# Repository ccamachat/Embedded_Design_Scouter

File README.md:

# ECE445L Final Lab

## Deliverables

The deliverables folder should contain documentation about your project as
outlined in the lab documents.

## HW

The hw folder should contain your schematic and board files for your PCB or
circuits. In labs 3-11, you will be creating schematics for your circuit
in EAGLE. A setup tutorial can be found
[here](https://www.shawnvictor.net/autodesk-eagle.html).

## SW

The sw folder should contain your application firmware and software written for
the lab. The sw/inc folder contains firmware drivers written for you by
Professor Valvano. Feel free to write your own (in fact, in some labs, you may
be required to write your own).

You can place any other source files in the sw/ folder. TAs will look at the
files you create and/or modify for software quality and for running your
project.

## Resources

A couple files are provided in the Resources folder so you don't have to keep
searching for that one TI document. Some of them are immediately useful, like
the TM4C datasheet. Others may be useful for your final project, like the
TM4C_System_Design_Guidelines page.

## Git and Github

We will extensively use Git and Github for managing lab projects. This makes it
easier for TAs to grade and help debug the project by allowing the students to
see commit histories, maintain a common project structure, collaborate with
partners, merge different codebases, and to debug work.

Two common ways of using Git and Github are [Github Desktop](https://desktop.github.com/) and the [command line](https://git-scm.com/downloads). [Tutorials](https://dev.to/mollynem/git-github--workflow-fundamentals-5496) are also abundant on the net for you to peruse. We've provided a cheatsheet for git in the Resources folder.

It is highly recommended to make the most out of Git, even if you've never used
it before. Version control will save you a lot of suffering, and tools like Git
or SVN are ubiquitous in the industry.

## Lab Report

Following the lab doc provided at the root of this project, the TAs request you
submit a lab report in Microsoft Word (or Pages, if you're a Mac user). Please
name it `EID_lab_LAB_NUMBER_report.pdf`. Templates are provided in the root dir.

## Team Members/ Contributors

Coty Camachat   - Physical Design & PCB Soldering/Verification, Code Review  
Neilan Garcia   - PCB Soldering, PCB Design, Code Review  
Ethan Syed      - Software encoding, Protocol Verification, Device Acquisition  
Phebe Tan       - Software encoding, documentation review  
Under Supervision of Profesor Jonathan Valvano

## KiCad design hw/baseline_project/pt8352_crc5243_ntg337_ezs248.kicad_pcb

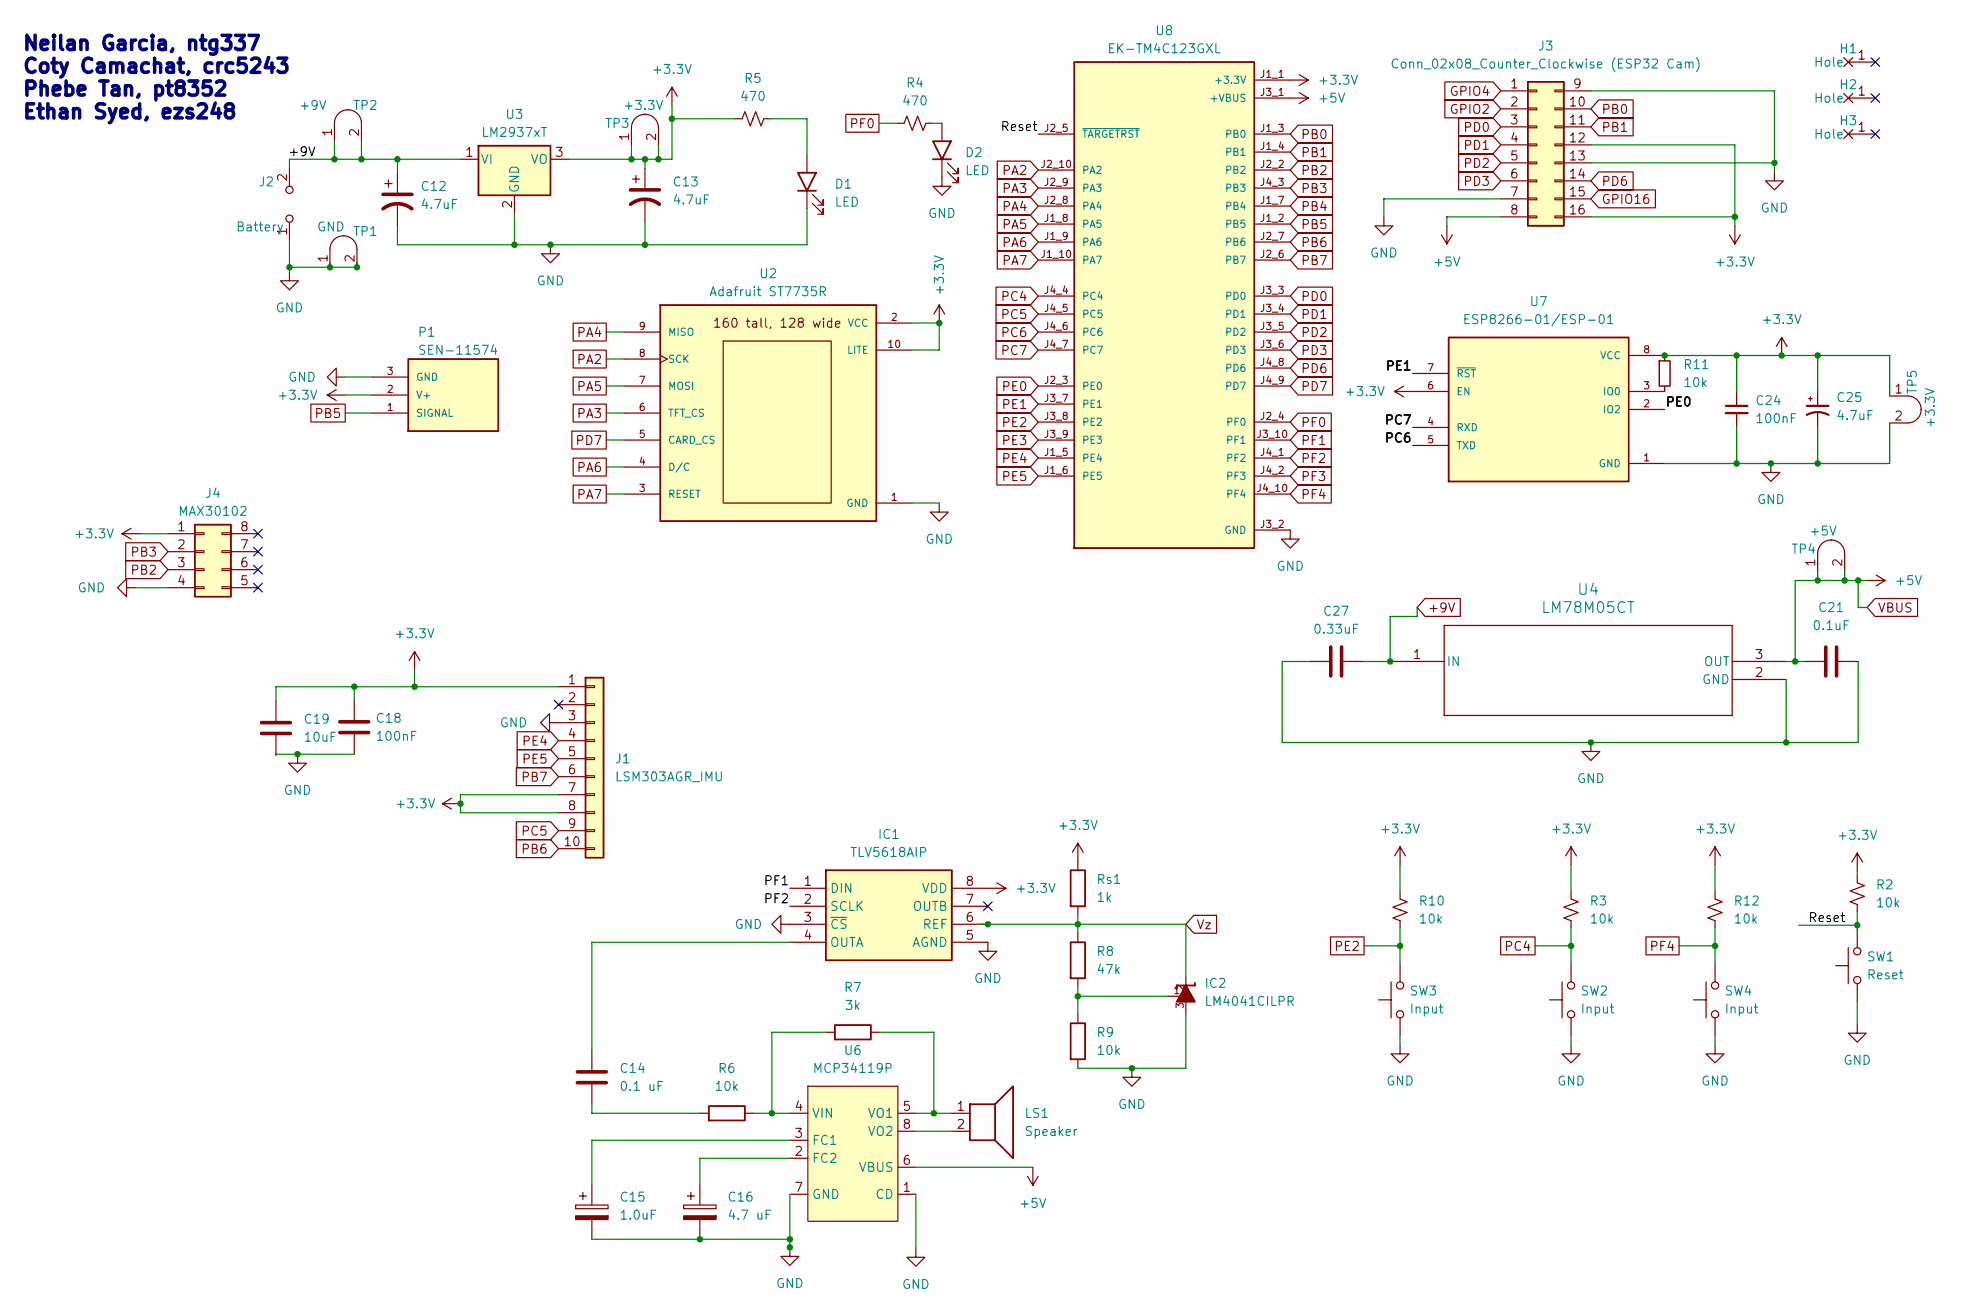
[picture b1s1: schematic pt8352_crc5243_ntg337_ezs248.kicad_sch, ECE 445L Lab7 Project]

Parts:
C12, C13, C25: 4.7uF; CP_Radial_Tantal200mil
C14: 0.1 uF; C_Axial_200mil
C15: 1.0uF; CP_Radial_Tantal200mil
C16: 4.7 uF; CP_Radial_Tantal200mil
C18, C24: 100nF; C_Axial_200mil
C19: 10uF; C_Axial_200mil
C21: 0.1uF; C_Axial_200mil
C27: 0.33uF; C_Axial_200mil
D1, D2: LED; LED_D5.0mm
H1, H2, H3: MountingHole_4_40
IC1: TLV5618AIP; DIP-8_W7.62mm_LongPads
IC2: LM4041CILPR; ti_LM4041CILPR
J1: LSM303AGR_IMU; Breakout_LSM303AGR_IMU
J2: Battery; Battery_Panasonic_CR1025-VSK_Vertical_CircularHoles
J3: Conn_02x08_Counter_Clockwise (ESP32 Cam); ESP32-CAM_v1
J4: MAX30102; MAX-30102_v1
LS1: Speaker; PinHeader_1x02_P2.54mm_Vertical
P1: SEN-11574; XDCR_SEN-11574
R2, R3, R6, R9, R10, R11, R12: 10k; R_Axial_DIN0204_L3.6mm_D1.6mm_P7.62mm_Horizontal
R4, R5: 470; R_Axial_DIN0204_L3.6mm_D1.6mm_P7.62mm_Horizontal
R7: 3k; R_Axial_DIN0204_L3.6mm_D1.6mm_P7.62mm_Horizontal
R8: 47k; R_Axial_DIN0204_L3.6mm_D1.6mm_P7.62mm_Horizontal
Rs1: 1k; R_Axial_DIN0204_L3.6mm_D1.6mm_P7.62mm_Horizontal
SW1: Reset; SW_PUSH_6mm
SW2, SW3, SW4: Input; SW_PUSH_6mm
TP1: GND; Testpoint_1x02_P2.54mm
TP2: +9V; Testpoint_1x02_P2.54mm
TP3, TP5: +3.3V; Testpoint_1x02_P2.54mm
TP4: +5V; Testpoint_1x02_P2.54mm
U2: Adafruit ST7735R; PinHeader_1x10_P2.54mm_Vertical
U3: LM2937xT; TO-220-3_Vertical
U4: LM78M05CT; T03B_TEX
U6: MCP34119P; DIP-8_W7.62mm_LongPads
U7: ESP8266-01/ESP-01; ai_thinker_ESP8266_01
U8: EK-TM4C123GXL; ti_EKTM4C123GXL

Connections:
+9V: C12.1, C27.2, J2.2 (B), TP2.1 (A), TP2.2 (B), U3.1 (VI), U4.1 (IN)
/Reset: R2.2, SW1.2, U8.J2_5 (~TARGETRST)
GPIO2: J3.2
GPIO4: J3.1
GPIO16: J3.15
unnamed: C14.2, R6.2
unnamed: D1.2 (A), R5.2
unnamed: D2.2 (A), R4.2
unnamed: C14.1, IC1.4 (OUTA)
unnamed: IC2.1, R8.2, R9.1
unnamed: C15.1, U6.3 (FC1)
unnamed: C16.1, U6.2 (FC2)
unnamed: R6.1, R7.2, U6.4 (VIN)
unnamed: LS1.1, R7.1, U6.5 (VO1)
unnamed: LS1.2, U6.8 (VO2)
unnamed: R11.2, U7.3 (IO0)
PA2: U2.8 (SCK), U8.J2_10 (PA2)
PA3: U2.6 (TFT_CS), U8.J2_9 (PA3)
PA4: U2.9 (MISO), U8.J2_8 (PA4)
PA5: U2.7 (MOSI), U8.J1_8 (PA5)
PA6: U2.4 (D/C), U8.J1_9 (PA6)
PA7: U2.3 (RESET), U8.J1_10 (PA7)
PB0: J3.10, U8.J1_3 (PB0)
PB1: J3.11, U8.J1_4 (PB1)
PB2: J4.3, U8.J2_2 (PB2)
PB3: J4.2, U8.J4_3 (PB3)
PB4: U8.J1_7 (PB4)
PB5: P1.1 (SIGNAL), U8.J1_2 (PB5)
PB6: J1.10, U8.J2_7 (PB6)
PB7: J1.6, U8.J2_6 (PB7)
PC4: R3.1, SW2.2, U8.J4_4 (PC4)
PC5: J1.9, U8.J4_5 (PC5)
PC6: U7.5 (TXD), U8.J4_6 (PC6)
PC7: U7.4 (RXD), U8.J4_7 (PC7)
PD0: J3.3, U8.J3_3 (PD0)
PD1: J3.4, U8.J3_4 (PD1)
PD2: J3.5, U8.J3_5 (PD2)
PD3: J3.6, U8.J3_6 (PD3)
PD6: J3.14, U8.J4_8 (PD6)
PD7: U2.5 (CARD_CS), U8.J4_9 (PD7)
PE0: U7.2 (IO2), U8.J2_3 (PE0)
PE1: U7.7 (~RST), U8.J3_7 (PE1)
PE2: R10.1, SW3.2, U8.J3_8 (PE2)
PE3: U8.J3_9 (PE3)
PE4: J1.4, U8.J1_5 (PE4)
PE5: J1.5, U8.J1_6 (PE5)
PF0: R4.1, U8.J2_4 (PF0)
PF1: IC1.1 (DIN), U8.J3_10 (PF1)
PF2: IC1.2 (SCLK), U8.J4_1 (PF2)
PF3: U8.J4_2 (PF3)
PF4: R12.1, SW4.2, U8.J4_10 (PF4)
VBUS: C21.1, J3.8, TP4.1 (A), TP4.2 (B), U4.3 (OUT), U6.6 (VBUS), U8.J3_1 (+VBUS)
Vz: IC1.6 (REF), IC2.2, R8.1, Rs1.2

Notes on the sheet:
Neilan Garcia, ntg337 Coty Camachat, crc5243 Phebe Tan, pt8352 Ethan Syed, ezs248

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
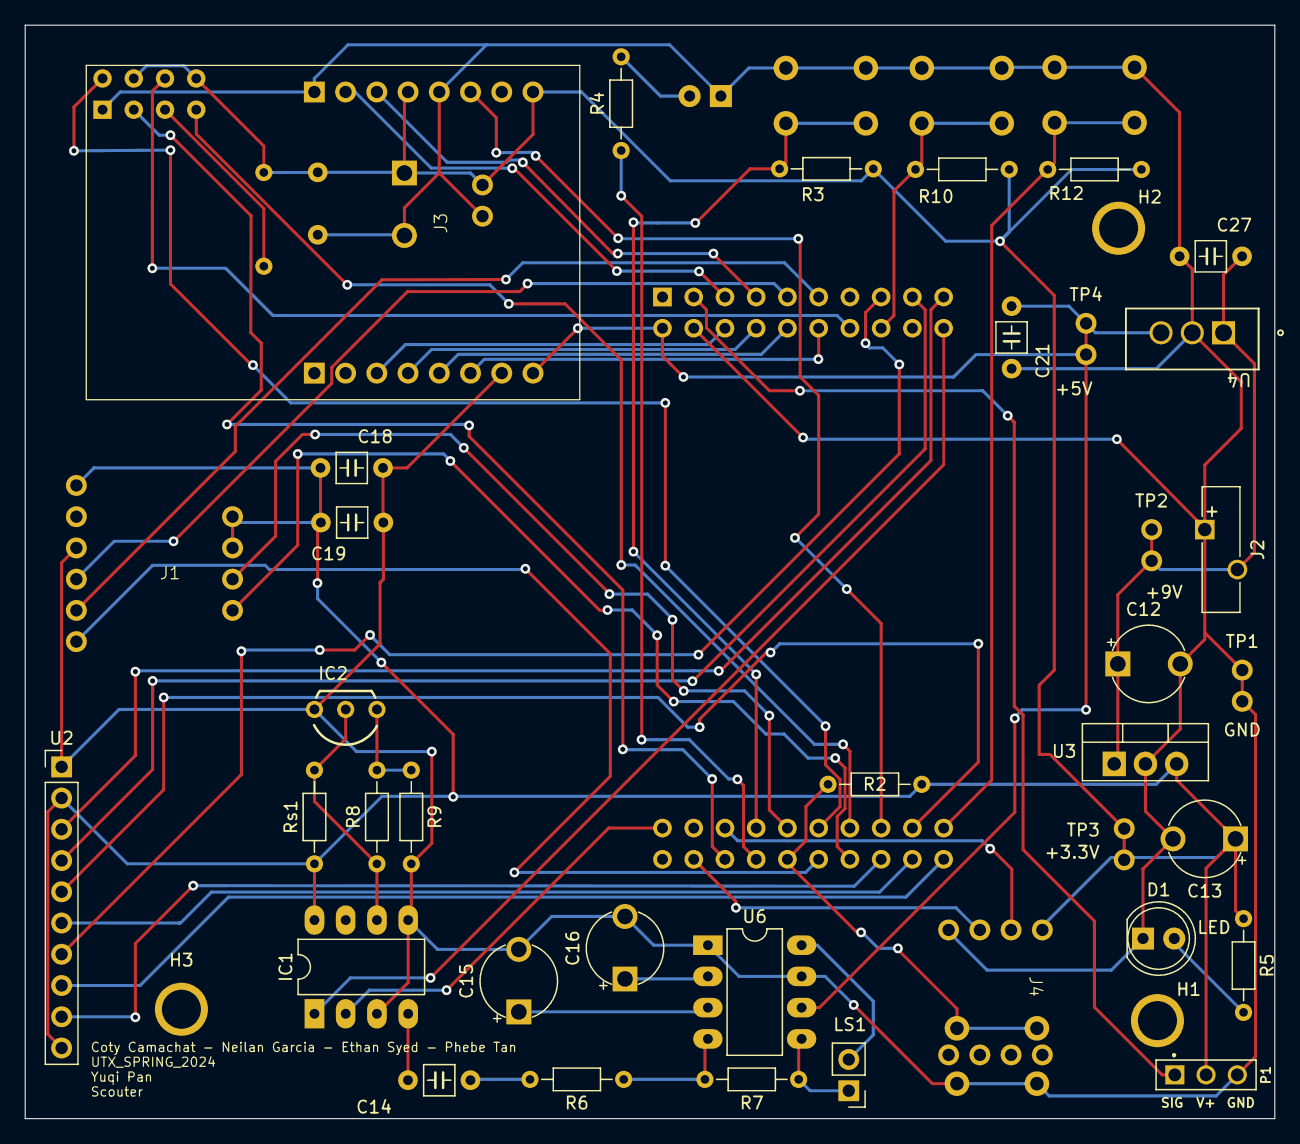
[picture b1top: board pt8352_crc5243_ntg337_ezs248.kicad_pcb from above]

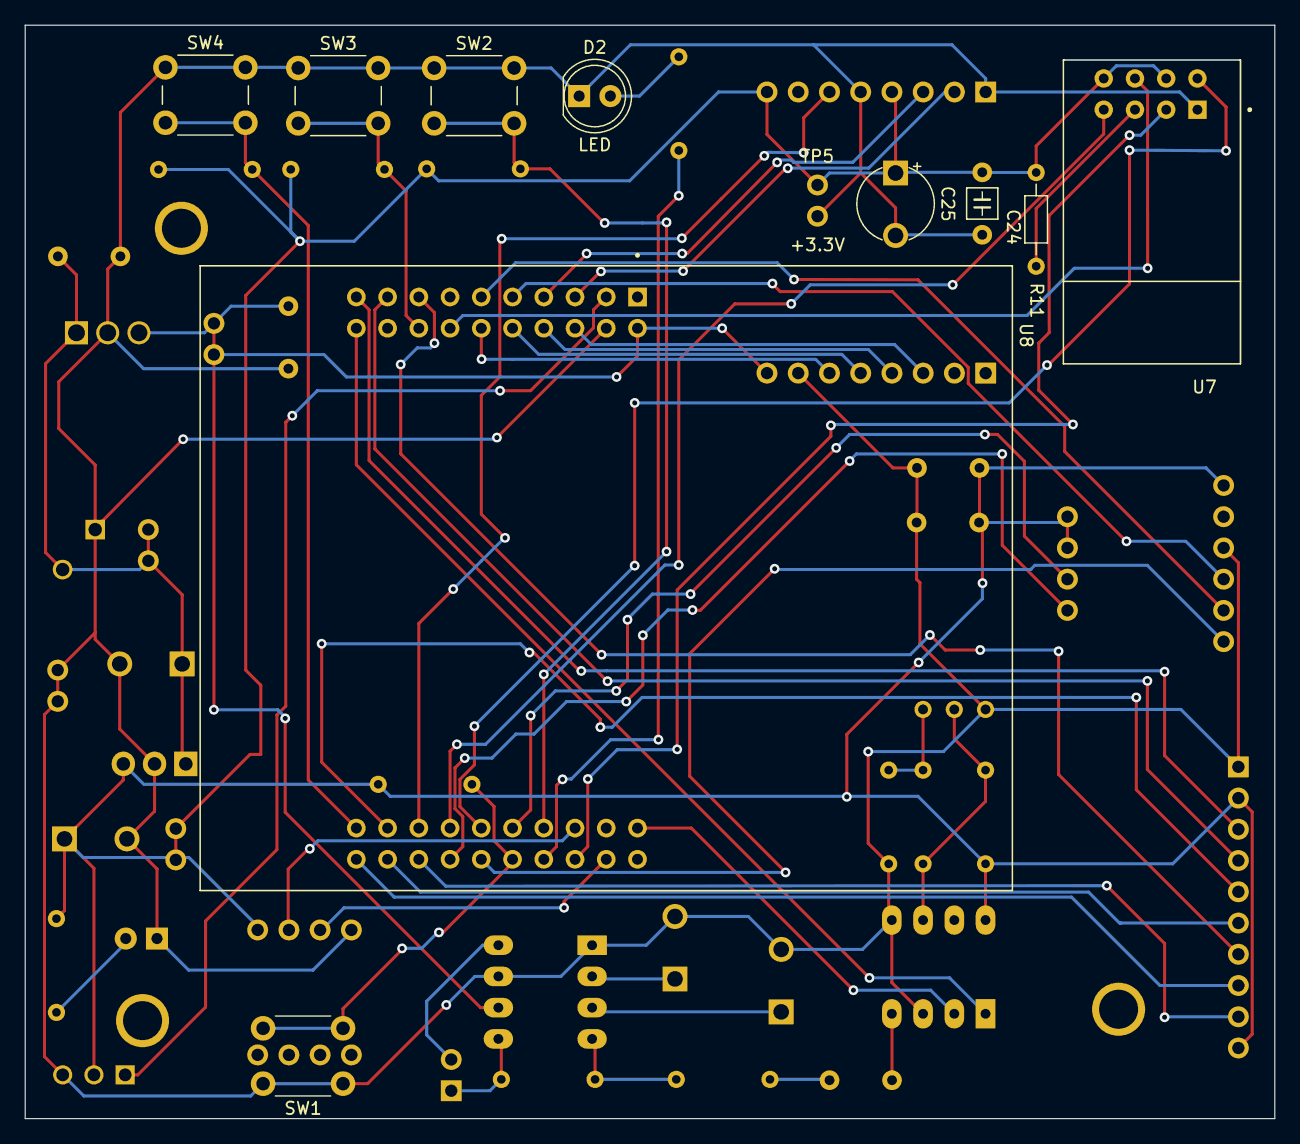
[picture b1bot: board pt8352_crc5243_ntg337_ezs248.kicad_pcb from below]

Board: 2 copper layers, 101.6 x 88.9 mm, 51 parts (11 on the bottom side), 49 nets.

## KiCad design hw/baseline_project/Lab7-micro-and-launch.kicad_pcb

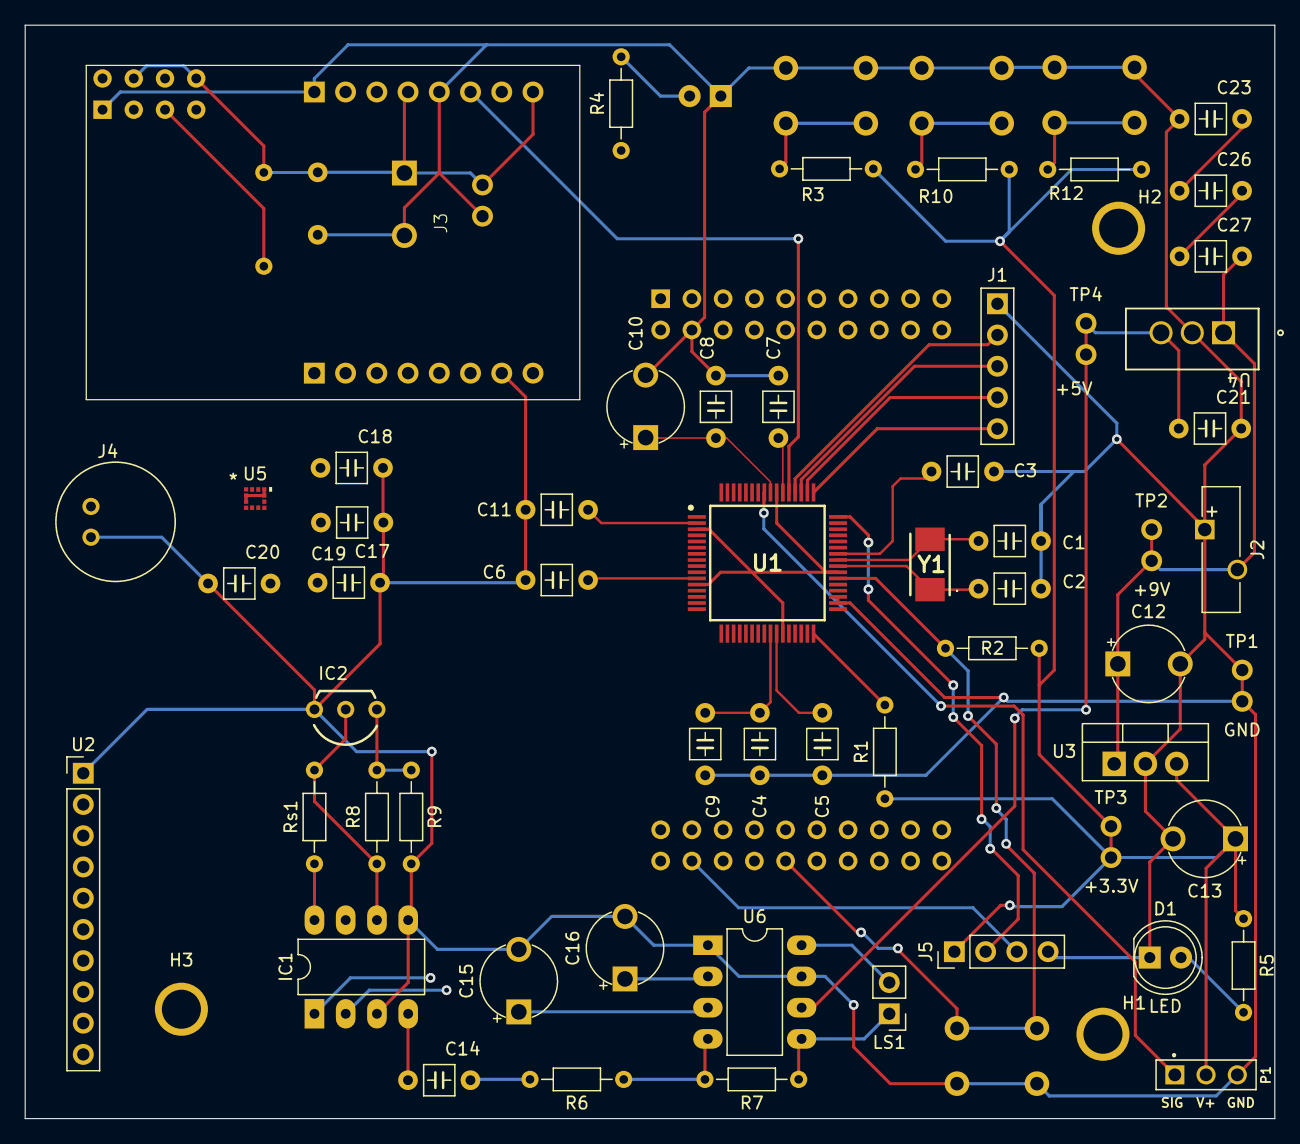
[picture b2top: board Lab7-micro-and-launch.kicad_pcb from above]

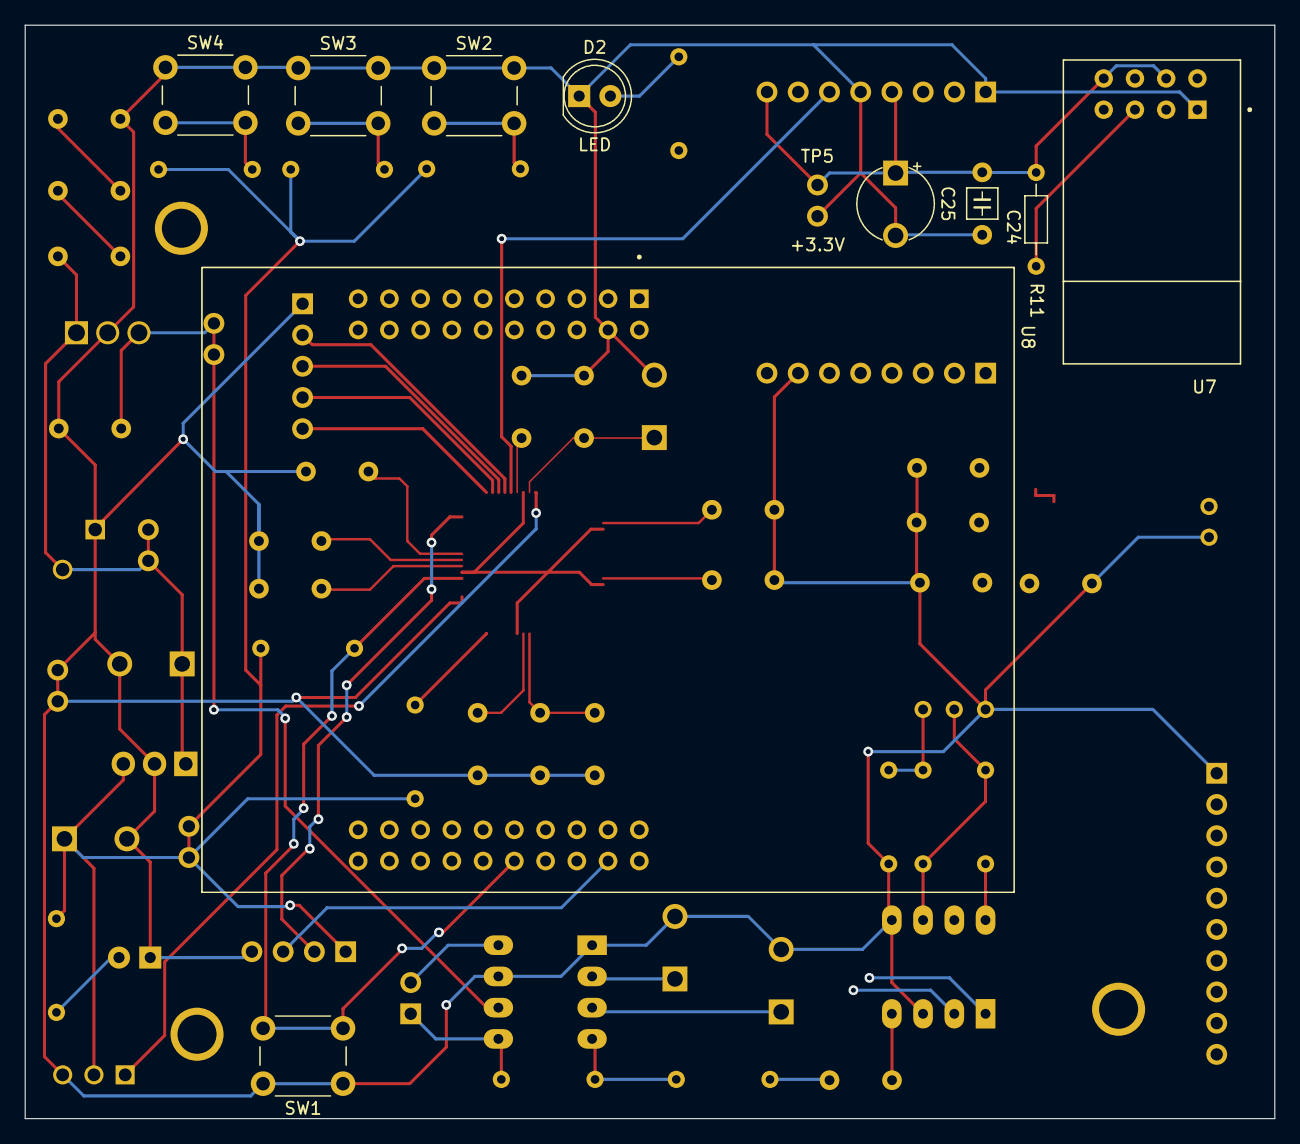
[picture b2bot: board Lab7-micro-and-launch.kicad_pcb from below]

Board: 2 copper layers, 101.6 x 88.9 mm, 71 parts (11 on the bottom side), 52 nets.

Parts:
C1, C2: 10pF C0G; C_Axial_200mil
C3, C9: 1uF; C_Axial_200mil
C4, C6, C7, C8, C21, C23, C26, C27: 0.1uF; C_Axial_200mil
C5, C11: 0.01uF; C_Axial_200mil
C10: 2.2uF; CP_Radial_Tantal200mil
C12, C13, C25: 4.7uF; CP_Radial_Tantal200mil
C14: 0.1 uF; C_Axial_200mil
C15: 1.0uF; CP_Radial_Tantal200mil
C16: 4.7 uF; CP_Radial_Tantal200mil
C17, C18, C24: 100nF; C_Axial_200mil
C19: 10uF; C_Axial_200mil
C20: 220nF; C_Axial_200mil
D1, D2: LED; LED_D5.0mm
H1, H2, H3: MountingHole_4_40
IC1: TLV5618AIP; DIP-8_W7.62mm_LongPads
IC2: LM4041CILPR; ti_LM4041CILPR
J1: JTAG; PinHeader_1x05_P2.54mm_Vertical
J2: Battery; Battery_Panasonic_CR1025-VSK_Vertical_CircularHoles
J3: Conn_02x08_Counter_Clockwise (ESP32 Cam); ESP32-CAM_v1
J4: Microphone; CUI_CMA-6542PF
J5: MAX30102; PinHeader_1x04_P2.54mm_Vertical
LS1: Speaker; PinHeader_1x02_P2.54mm_Vertical
P1: SEN-11574; XDCR_SEN-11574
R1: 1M; R_Axial_DIN0204_L3.6mm_D1.6mm_P7.62mm_Horizontal
R2, R3, R6, R9, R10, R11, R12: 10k; R_Axial_DIN0204_L3.6mm_D1.6mm_P7.62mm_Horizontal
R4, R5: 470; R_Axial_DIN0204_L3.6mm_D1.6mm_P7.62mm_Horizontal
R7: 3k; R_Axial_DIN0204_L3.6mm_D1.6mm_P7.62mm_Horizontal
R8: 47k; R_Axial_DIN0204_L3.6mm_D1.6mm_P7.62mm_Horizontal
Rs1: 1k; R_Axial_DIN0204_L3.6mm_D1.6mm_P7.62mm_Horizontal
SW1: Reset; SW_PUSH_6mm
SW2, SW3, SW4: Input; SW_PUSH_6mm
TP1: GND; Testpoint_1x02_P2.54mm
TP2: +9V; Testpoint_1x02_P2.54mm
TP3, TP5: +3.3V; Testpoint_1x02_P2.54mm
TP4: +5V; Testpoint_1x02_P2.54mm
U1: TM4C123GH6PMIR; QFP50P1200X1200X160-64N
U2: Adafruit ST7735R; PinHeader_1x10_P2.54mm_Vertical
U3: LM2937xT; TO-220-3_Vertical
U4: LM78M05CT; T03B_TEX
U5: LSM303AGRTR; SON_03AGRTR_STM
U6: MCP34119P; DIP-8_W7.62mm_LongPads
U7: ESP8266-01/ESP-01; ai_thinker_ESP8266_01
U8: EK-TM4C123GXL; ti_EKTM4C123GXL
Y1: ABM3-16.000MHZ-B2-T; ABM3

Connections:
+3.3V: C3.1, C5.1, C6.1, C7.1, C11.1, C13.1, C17.1, C18.1, C19.2, C24.1, C25.1, IC1.8 (VDD), J3.12, J3.16, J5.1, P1.2 (V+), R1.1, R2.1, R3.2, R5.1, R10.2, R11.1, R12.2, Rs1.1, TP3.1 (A), TP3.2 (B), TP5.1 (A), U1.2 (VDDA), U1.11 (VDD_1), U1.26 (VDD_2), U1.37 (VBAT), U1.42 (VDD_3), U1.54 (VDD_4), U2.2 (VCC), U2.10 (LITE), U3.3 (VO), U5.2 (CS_XL), U5.3 (CS_MAG), U5.9 (VDD), U5.10 (VDD_IO), U7.6 (EN), U7.8 (VCC), U8.J1_1 (+3.3V)
+9V: C12.1, C27.2, J2.2 (B), TP2.1 (A), TP2.2 (B), U3.1 (VI), U4.1 (IN)
/LDO: C4.1, C8.1, C9.1, C10.1, U1.25 (VDDC_1), U1.56 (VDDC_2)
/OSC1: C1.1, U1.41 (OSC1), Y1.2
/OSC2: C2.1, U1.40 (OSC0), Y1.1
/Reset: R2.2, SW1.2, U1.38 (~RST), U8.J2_5 (~TARGETRST)
/TCK: J1.2 (B), U1.52 (PC0/TCK/SWCLK)
/TDI: J1.4 (C), U1.50 (PC2/TDI)
/TDO: J1.5 (C), U1.49 (PC3/TDO/SWO)
/TMS: J1.3 (C), U1.51 (PC1/TMS/SWDIO)
GND: C1.2, C2.2, C3.2, C4.2, C5.2, C6.2, C7.2, C8.2, C9.2, C10.2, C11.2, C12.2, C13.2, C15.2, C16.2, C17.2, C18.2, C19.1, C20.1, C21.2, C23.1, C24.2, C25.2, D1.1 (K), D2.1 (K), IC1.3 (~CS), IC1.5 (AGND), IC2.3, J1.1 (A), J2.1 (A), J3.7, J3.9, J3.13, J4.2, J5.4, P1.3 (GND), R9.2, SW1.1, SW2.1, SW3.1, SW4.1, TP1.1 (A), TP1.2 (B), TP5.2 (B), U1.3 (GNDA), U1.12 (GND_1), U1.27 (GND_2), U1.34 (XOSC0), U1.35 (GNDX), U1.39 (GND_3), U1.55 (GND_4), U2.1 (GND), U3.2 (GND), U4.2 (GND), U5.8 (GND), U6.1 (CD), U6.7 (GND), U7.1 (GND), U8.J3_2 (GND)
unnamed: D1.2 (A), R5.2
unnamed: D2.2 (A), R4.2
unnamed: C14.1, IC1.4 (OUTA)
unnamed: IC2.1, R8.2, R9.1
PA2: U1.19 (PA2/SSI0C1K), U2.8 (SCK), U8.J2_10 (PA2)
PA3: U1.20 (PA3/SSI0FSS), U2.6 (TFT_CS), U8.J2_9 (PA3)
PA4: U1.21 (PA4/SSI0RX), U2.9 (MISO), U8.J2_8 (PA4)
PA5: U1.22 (PA5/SSI0TX), U2.7 (MOSI), U8.J1_8 (PA5)
PA6: U1.23 (PA6), U2.4 (D/C), U8.J1_9 (PA6)
PA7: U1.24 (PA7), U2.3 (RESET), U8.J1_10 (PA7)
PB0: J3.10, U1.45 (PB0/USB0ID), U8.J1_3 (PB0)
PB1: J3.11, U1.46 (PB1/USB0VBUS), U8.J1_4 (PB1)
PB2: J5.3, U1.47 (PB2/I2C0SCL), U8.J2_2 (PB2)
PB3: J5.2, U1.48 (PB3/I2C0SDA), U8.J4_3 (PB3)
PB4: U1.58 (PB4), U8.J1_7 (PB4)
PB5: P1.1 (SIGNAL), U1.57 (PB5), U8.J1_2 (PB5)
PB6: U1.1 (PB6), U5.11 (INT_2_XL), U8.J2_7 (PB6)
PB7: U1.4 (PB7), U5.7 (INT_MAG/DRDY), U8.J2_6 (PB7)
PC4: R3.1, SW2.2, U1.16 (PC4), U8.J4_4 (PC4)
PC5: U1.15 (PC5), U5.12 (INT_1_XL), U8.J4_5 (PC5)
PC6: U1.14 (PC6), U7.5 (TXD), U8.J4_6 (PC6)
PC7: U1.13 (PC7), U7.4 (RXD), U8.J4_7 (PC7)
PD0: J3.3, U1.61 (PD0), U8.J3_3 (PD0)
PD1: J3.4, U1.62 (PD1)
PD2: J3.5, U1.63 (PD2), U8.J3_4 (PD1), U8.J3_5 (PD2)
PD3: J3.6, U1.64 (PD3), U8.J3_6 (PD3)
PD6: J3.14, U1.53 (PD6), U8.J4_8 (PD6)
PD7: U1.10 (PD7), U2.5 (CARD_CS), U8.J4_9 (PD7)
PE0: U1.9 (PE0), U7.2 (IO2), U8.J2_3 (PE0)
PE1: U1.8 (PE1), U7.7 (~RST), U8.J3_7 (PE1)
PE2: R10.1, SW3.2, U1.7 (PE2), U8.J3_8 (PE2)
PE3: J4.1, U1.6 (PE3), U8.J3_9 (PE3)
PE4: U1.59 (PE4), U5.1 (SCL/SPC), U8.J1_5 (PE4)
PE5: U1.60 (PE5), U5.4 (SDA/SDI/SDO), U8.J1_6 (PE5)
PF0: R4.1, U1.28 (PF0), U8.J2_4 (PF0)
PF1: IC1.1 (DIN), U1.29 (PF1), U8.J3_10 (PF1)
PF2: IC1.2 (SCLK), U1.30 (PF2), U8.J4_1 (PF2)
PF3: U1.31 (PF3), U8.J4_2 (PF3)
PF4: R12.1, SW4.2, U1.5 (PF4), U8.J4_10 (PF4)
VBUS: C21.1, J3.8, TP4.1 (A), TP4.2 (B), U4.3 (OUT), U6.6 (VBUS), U8.J3_1 (+VBUS)
Vz: IC1.6 (REF), IC2.2, R8.1, Rs1.2

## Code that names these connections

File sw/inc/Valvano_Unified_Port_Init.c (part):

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// Port A drives the ST7735 LCD 
//
// Backlight (pin 10) connected to +3.3 V
// MISO      (pin 9)  connected to PA4
// SCK       (pin 8)  connected to PA2 (SSI0Clk)
// MOSI      (pin 7)  connected to PA5 (SSI0Tx)
// TFT_CS    (pin 6)  connected to PA3 (SSI0Fss)
// CARD_CS   (pin 5)  connected to PB0 (GPIO)
// Data/CMD  (pin 4)  connected to PA6 (GPIO), high for data, low for command
// RESET     (pin 3)  connected to PA7 (GPIO)
// VCC       (pin 2)  connected to +3.3 V
// Gnd       (pin 1)  connected to ground
//
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  SYSCTL_RCGCGPIO_R     |= 0x01;            // Activate port A
  while((SYSCTL_PRGPIO_R & 0x01)==0){};     // allow time for clock to start
    
  GPIO_PORTA_DIR_R      |= 0xC8;            // make PA3,6,7 out
  GPIO_PORTA_AFSEL_R    &= ~0xC8;           // disable alt funct on PA3,6,7
  GPIO_PORTA_DEN_R      |= 0xC8;            // enable digital I/O on PA3,6,7
  
  // configure PA3,6,7 as GPIO
  GPIO_PORTA_PCTL_R      = (GPIO_PORTA_PCTL_R
                         & 0x00FF0FFF)
                         + 0x00000000;
  
  GPIO_PORTA_AMSEL_R    &= ~0xC8;           // disable analog functionality on PA3,6,7

  // initialize SSI0
  GPIO_PORTA_AFSEL_R    |= 0x2C;            // enable alt funct on PA2,3,5
  GPIO_PORTA_DEN_R      |= 0x2C;            // enable digital I/O on PA2,3,5
 
  // configure PA2,3,5 as SSI
  GPIO_PORTA_PCTL_R      = (GPIO_PORTA_PCTL_R
                         & 0xFF0F00FF)
                         + 0x00202200;
  
  GPIO_PORTA_AMSEL_R    &= ~0x2C;           // disable analog functionality on PA2,3,5
  SSI0_CR1_R            &= ~SSI_CR1_SSE;    // disable SSI
  SSI0_CR1_R            &= ~SSI_CR1_MS;     // master mode
  
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// ----------------    PORT B Initialization   --------------------------------
// ----------------------------------------------------------------------------
//
// PB7 = PWM Ouptut to JP6 (M0PWM1)
// PB6 = PWM Output to Motor (M0PWM0)
// PB5 = ADC Input (AIN11)
// PB4 = Timer Capture input (T1CCP0)
// PB3 = GPIO 
// PB2 = GPIO/I2C0
// PB1 = GPIO/I2C0CL
// PB0 = ST7735 Card CS

void Port_B_Init(void){ 
  
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  SYSCTL_RCGCGPIO_R     |= 0x02;            // activate port B
  while((SYSCTL_PRGPIO_R & 0x02) == 0){};   // Wait
  
  // ---------------  Initialize PB7 as M0PWM1  -----------------------  

  GPIO_PORTB_AFSEL_R    |=  0x80;           // enable alt funct on PB7
  GPIO_PORTB_PCTL_R     &= ~0xF0000000;     // configure PB7 as M0PWM1
  GPIO_PORTB_PCTL_R     |=  0x40000000;
  GPIO_PORTB_AMSEL_R    &= ~0x80;           // disable analog functionality on PB7
  GPIO_PORTB_DEN_R      |=  0x80;           // enable digital I/O on PB7

  // ---------------  Initialize PB6 as M0PWM0  -----------------------
  GPIO_PORTB_AFSEL_R    |=  0x40;           // enable alt funct on PB6
  GPIO_PORTB_PCTL_R     &= ~0x0F000000;     // configure PB6 as PWM0
  GPIO_PORTB_PCTL_R     |=  0x04000000;  
  GPIO_PORTB_AMSEL_R    &= ~0x40;           // disable analog functionality on PB6
  GPIO_PORTB_DEN_R      |=  0x40;           // enable digital I/O on PB6
  
  // ---------------  Initialize PB5 as AIN11  ----------------------- 
  GPIO_PORTB_DIR_R      &= ~0x20;           // make PB5 input
  GPIO_PORTB_AFSEL_R    |=  0x20;           // enable alternate function on PB5
  GPIO_PORTB_DEN_R      &= ~0x20;           // disable digital I/O on PB5
  GPIO_PORTB_AMSEL_R    |=  0x20;           // enable analog functionality on PB5

  // ----------------- Initialize PB4 as Timer Capture input (T1CCP0) ---------
  GPIO_PORTB_DIR_R      &= ~0x10;           // make PB4 input
  GPIO_PORTB_AFSEL_R    |= 0x10;            // enable alt funct on PB4
  GPIO_PORTB_DEN_R      |= 0x10;            // enable digital I/O on PB4
                                            // configure PB4 (T1CCP0)
  GPIO_PORTB_PCTL_R     = (GPIO_PORTB_PCTL_R 
                        &  0xFFF0FFFF)
                        +  0x00070000;
  GPIO_PORTB_AMSEL_R    &= ~0x10;           // disable analog functionality on PB4

  // ----------------- Initialize PB3-0 as GPIO ---------
                                      
																			//TODO: make PB2 an input switch.
  GPIO_PORTB_PCTL_R     &= ~0x0000FFFF;     // GPIO
  GPIO_PORTB_DIR_R      |=  0x0F;           // make PB3-0 out
  GPIO_PORTB_AFSEL_R    &= ~0x0F;           // regular port function
  GPIO_PORTB_DEN_R      |=  0x0F;           // enable digital I/O on PB3-0
  GPIO_PORTB_AMSEL_R    &= ~0x0F;           // disable analog functionality on PB3-0
  
  
  }
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// ----------------    PORT C Initialization   --------------------------------
// ----------------------------------------------------------------------------
//
// PC4 = UP switch
// PC5 = RIGHT switch
// PC6 = LEFT switch
// PC7 = DOWN switch
//

void Port_C_Init(void){ 
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   
  GPIO_PORTC_PCTL_R     &= ~0xFFFF0000;   // regular GPIO
  GPIO_PORTC_AMSEL_R    &= ~0xF0;         // disable analog function 
  GPIO_PORTC_DIR_R      &= ~0xF0;         // inputs on PC7-PC4
  GPIO_PORTC_AFSEL_R    &= ~0xF0;         // regular port function
  GPIO_PORTC_PUR_R       =  0xF0;         // enable pull-up on PC7-PC4
  GPIO_PORTC_DEN_R      |=  0xF0;         // enable digital port 
  }  
  
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// ----------------    PORT D Initialization   --------------------------------
// ----------------------------------------------------------------------------
//
// PD7 = U2TX
// PD6 = U2RX
// PD3 = SSI1_MOSI  (to TLV5616)
// PD2 = AIN5 (Monitor DAC_OUT signal from TLV5616)
// PD1 = SSI1_FS/CS (to TLV5616)
// PD0 = SSI1_SCK   (to TLV5616)
  
void Port_D_Init(void){
 
  SYSCTL_RCGCGPIO_R     |= 0x08;            // activate port D
  while((SYSCTL_PRGPIO_R & 0x08)==0){};     // allow time for clock to stabilize

  // ---------------  Initialize PB7 as U2TX, PB6 as U2RX  -----------------------  
    
  GPIO_PORTD_LOCK_R      = 0x4C4F434B;      // unlock REQUIRED for PD7
  GPIO_PORTD_CR_R       |= 0xC0;            // commit PD6, PD7
  
  GPIO_PORTD_AMSEL_R    &= ~0xC0;           // disable analog functionality on PD6, PD7
  GPIO_PORTD_AFSEL_R    |=  0xC0;           // enable alternate function on PD6, PD7
  GPIO_PORTD_DEN_R      |=  0xC0;           // enable digital on PD6, PD7 (PD6 is U2RX, PD7 is U2TX)
  GPIO_PORTD_PCTL_R      =(GPIO_PORTD_PCTL_R  
                         & 0x00FFFFFF)
                         | 0x11000000;      // configure PD6, PD7 as UART
 
   // ---------------  Initialize PD2 as AIN5  ----------------------------------  
   
  GPIO_PORTD_DIR_R      &= ~0x04;           // make PD2 input
  GPIO_PORTD_AFSEL_R    |=  0x04;           // enable alternate function on PD2
  GPIO_PORTD_DEN_R      &= ~0x04;           // disable digital I/O on PD2
  GPIO_PORTD_AMSEL_R    |=  0x04;           // enable analog functionality on PD2

  // ---------------  Initialize PD3,1,0 as SSI1 MOSI, FS & SCK  ---------------- 
    
  GPIO_PORTD_AMSEL_R    &= ~0x0B;           // disable analog functionality on PD
  GPIO_PORTD_AFSEL_R    |=  0x0B;           // enable alt funct on PD3,1,0
  GPIO_PORTD_DEN_R      |=  0x0B;           // enable digital I/O on PD3,1,0
  GPIO_PORTD_PCTL_R      = (GPIO_PORTD_PCTL_R
                          & 0xFFFF0F00)
                          + 0x00002022;
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// ----------------    PORT E Initialization   --------------------------------
// ----------------------------------------------------------------------------
//
// PE5 = U5TX
// PE4 = U5RX
// PE3 = Heartbeat LED
// PE2 = AIN_1 (DAC_OUT Monitor)
// PE1 = RSTB_8266
// PE0 = 8266_ GPIO_2 

void Port_E_Init(void){

  SYSCTL_RCGCGPIO_R     |= 0x10;            // activate port E
  while((SYSCTL_PRGPIO_R & 0x10)==0){};

 // ---------------  Initialize PE5 as U5TX, PE4 as U5RX  -----------------------  

  GPIO_PORTE_AFSEL_R    |= 0x30;            // enable alt funct on PE5-4
  GPIO_PORTE_DEN_R      |= 0x30;            // enable digital I/O on PE5-4
                                            // configure PE5-4 as UART
  GPIO_PORTE_PCTL_R      = (GPIO_PORTE_PCTL_R
                         & 0xFF00FFFF)
                         + 0x00110000;
  GPIO_PORTE_AMSEL_R    &= ~0x30;           // disable analog functionality on PE

 // ---------------  Initialize PE3,1,0 as GPIO  ---------------------------------  

  GPIO_PORTE_DIR_R      |=  0x0A;           // output digital I/O on PE3,1
  GPIO_PORTE_DIR_R      &= ~0x01;           // input digital I/O on PE0
  GPIO_PORTE_AMSEL_R    &= ~0x0B;           // disable analog functionality on PE3,1,0
  GPIO_PORTE_AFSEL_R    &= ~0x0B;           // disable alt funct on PE3,1,0
  GPIO_PORTE_DEN_R      |=  0x0B;           // enable digital I/O on PE3,1,0
  
  GPIO_PORTE_PCTL_R      = (GPIO_PORTE_PCTL_R 
                         & 0xFFFF0F00);
  
// ---------------  Initialize PE2 as AIN1  ---------------------------------  
  
  GPIO_PORTE_DIR_R      &= ~0x04;           // make PE2 input
  GPIO_PORTE_AFSEL_R    |=  0x04;           // enable alternate function on PE2
  GPIO_PORTE_DEN_R      &= ~0x04;           // disable digital I/O on PE2
  GPIO_PORTE_AMSEL_R    |=  0x04;           // enable analog functionality on PE2
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
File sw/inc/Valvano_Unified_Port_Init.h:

#pragma once
// PORT-F  LaunchPAD switches and LEDS
//
#define PF0       (*((volatile uint32_t *)0x40025004))    // SW2
#define PF1       (*((volatile uint32_t *)0x40025008))    // RED LED
#define PF2       (*((volatile uint32_t *)0x40025010))    // BLUE LED
#define PF3       (*((volatile uint32_t *)0x40025020))    // GREEN LED
#define PF4       (*((volatile uint32_t *)0x40025040))    // SW1

// PORT-E
//
#define PE0       (*((volatile uint32_t *)0x40024004))
#define PE1       (*((volatile uint32_t *)0x40024008))
#define PE2       (*((volatile uint32_t *)0x40024010))
#define PE3       (*((volatile uint32_t *)0x40024020))    // Heartbeat LED
#define PE4       (*((volatile uint32_t *)0x40024040))
#define PE5       (*((volatile uint32_t *)0x40024080))

// PORT-D
//
#define PD0       (*((volatile uint32_t *)0x40007004))
#define PD1       (*((volatile uint32_t *)0x40007008))
#define PD2       (*((volatile uint32_t *)0x40007010))
#define PD3       (*((volatile uint32_t *)0x40007020))
#define PD6       (*((volatile uint32_t *)0x40007100))
#define PD7       (*((volatile uint32_t *)0x40007200))

// PORT-C Lab Board switches
//
#define PC4       (*((volatile uint32_t *)0x40006040))    // UP    and Logic Analyzer JP2-15
#define PC5       (*((volatile uint32_t *)0x40006080))    // RIGHT and Logic Analyzer JP2-13
#define PC6       (*((volatile uint32_t *)0x40006100))    // LEFT  and Logic Analyzer JP2-11
#define PC7       (*((volatile uint32_t *)0x40006200))    // DOWN  and Logic Analyzer JP2-9

// PORT-B
//
#define PB0       (*((volatile uint32_t *)0x40005004))     
#define PB1       (*((volatile uint32_t *)0x40005008))    // Logic Analyzer JP1-9
#define PB2       (*((volatile uint32_t *)0x40005010))
#define PB3       (*((volatile uint32_t *)0x40005020))
#define PB4       (*((volatile uint32_t *)0x40005040))     
#define PB5       (*((volatile uint32_t *)0x40005080))     
#define PB6       (*((volatile uint32_t *)0x40005100))     
#define PB7       (*((volatile uint32_t *)0x40005200))

// Switch definitions 

#define LEFT      PC6     // Switch on Lab Board
#define RIGHT     PC5     // Switch on Lab Board
#define UP        PC4     // Switch on Lab Board
#define DOWN      PC7     // Switch on Lab Board

#define MODE      PF4     // SW1 on the Launch Pad
#define SW1       PF4     // SW1 on the Launch Pad
#define SW2       PF0     // SW2 on the Launch Pad

// Prototypes for Port Inits

void Valvano_Unified_Port_Init(void);

void Port_A_Init(void);
void Port_B_Init(void);
void Port_C_Init(void);
void Port_D_Init(void);
void Port_E_Init(void);
void Port_F_Init(void);

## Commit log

2025-07-14 Initial import.
